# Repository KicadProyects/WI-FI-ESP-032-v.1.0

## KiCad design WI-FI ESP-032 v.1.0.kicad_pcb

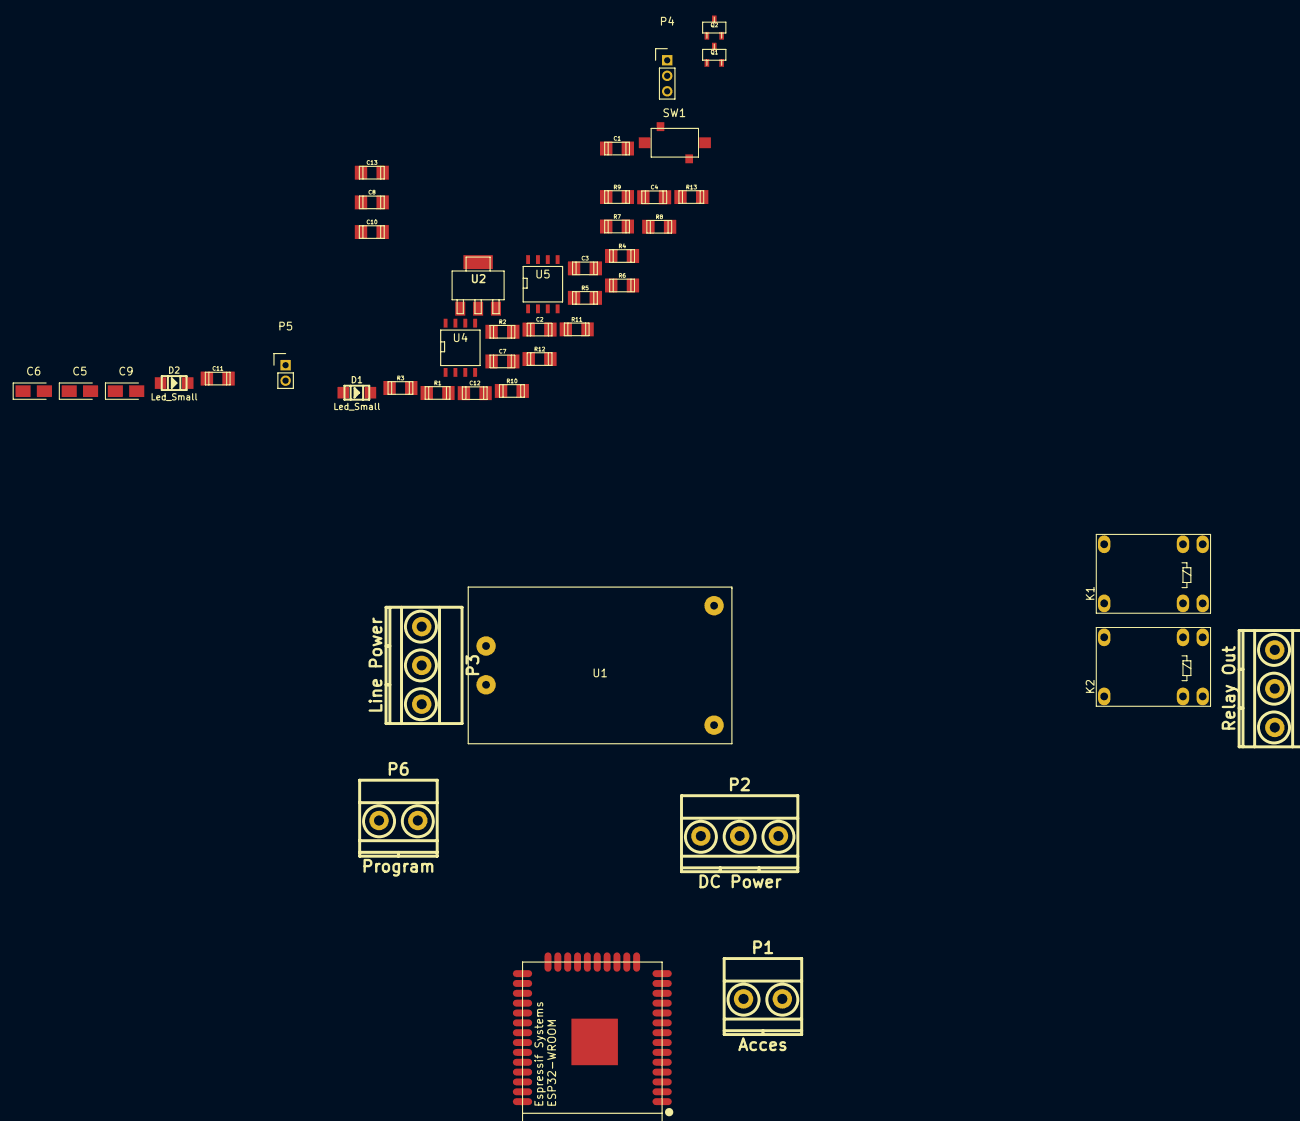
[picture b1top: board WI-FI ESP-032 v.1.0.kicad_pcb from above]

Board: 2 copper layers, 45 parts (0 on the bottom side), 31 nets, no tracks yet.

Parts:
C1, C2, C7, C8: C_Small; c_1206
C3, C11, C13: 1nF; c_1206
C4: 100uF; c_1206
C5: 1uF; CP_Tantalum_Case-A_EIA-3216-18_Reflow
C6: 10uF; CP_Tantalum_Case-A_EIA-3216-18_Reflow
C9: 22uF; CP_Tantalum_Case-A_EIA-3216-18_Reflow
C10, C12: 100pF; c_1206
D1, D2: Led_Small; Led_1206
K1, K2: TIANBO-HJR-4102; Relay_SPDT_HJR-4102
P1: Acces; mkds_1,5-2
P2: DC Power; mkds_1,5-3
P3: Line Power; mkds_1,5-3
P4: Light SWs; Pin_Header_Straight_1x03_Pitch2.00mm
P5: UART Download; Pin_Header_Straight_1x02_Pitch2.00mm
P6: Program; mkds_1,5-2
P7: Relay Out; mkds_1,5-3
Q1, Q2: BC817-40; sot23
R1, R2, R5, R6, R8, R9: R; r_1206
R3: 12K; r_1206
R4, R7: 5K; r_1206
R10, R11: 1K; r_1206
R12, R13: 250; r_1206
SW1: Reset SW; Switch_Sunrom
U1: HiLink_HLK-PM01; HLK-PM01
U2: LD1117S33TR; sot223
U3: ESP32-WROOM
U4, U5: ACS712; SOIC-8-N

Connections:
+3V3: C4.1, C5.1, C8.1, C9.1, P2.3, R1.1, R2.1, R3.1, R7.1, U2.2, U3.2
+5V: C6.1, C7.1, C10.2, C12.2, K1.5, K2.5, P2.1, R8.1, R9.1, U1.4, U2.3, U4.8, U5.8
ADC_1: R11.1, R13.1, U3.29
ADC_2: R10.1, R12.1, U3.31
Enable/Reset: C3.1, R3.2, SW1.2, U3.3
GND: C1.2, C2.2, C3.2, C4.2, C5.2, C6.2, C7.2, C8.2, C9.2, C10.1, C11.1, C12.1, C13.1, P2.2, P5.2, P6.1, Q1.2, Q2.2, R4.2, R12.2, R13.2, SW1.1, U1.3, U2.1, U3.1, U3.15, U3.38, U4.5, U5.5
Lin: P3.1, U1.1, U4.1, U4.2, U5.1, U5.2
unnamed: C11.2, U4.6
unnamed: C13.2, U5.6
unnamed: D1.1, K1.8, Q1.3
unnamed: D1.2, R8.2
unnamed: D2.1, K2.8, Q2.3
unnamed: D2.2, R9.2
unnamed: Q1.1, R5.1
unnamed: Q2.1, R6.1
unnamed: R4.1, U3.24
unnamed: R10.2, U5.7
unnamed: R11.2, U4.7
Neu: P3.2, U1.2
Out-712(1): K1.12, U4.3, U4.4
Out-712(2): K2.12, U5.3, U5.4
PIR: P1.2, U3.6
Program: P6.2, R7.2, U3.25
RLY1: K1.6, P7.1
RLY2: K2.6, P7.2
Rel_K1: R5.2, U3.37
Rel_K2: R6.2, U3.36
S1: C1.1, P4.2, R1.2, U3.14
S2: C2.1, P4.1, R2.2, U3.13
TXD: P5.1, U3.35
°C: P1.1, U3.27

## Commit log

2017-11-19 :confetti_ball: Added .gitattributes & .gitignore files
